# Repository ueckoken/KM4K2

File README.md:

# KagiMod for Koken ver.2 (KM4K2)

KagiMod for Kokenを元にして認証機能を切り離したものです。

RedisにIdmをキャッシュすることによって高速な認証を実現しています。

### Launch

KM4K.serviceはsystemdに登録されています。

```
systemctl status KM4K2
```

で確認

### 環境変数

- `CARD_MANAGER_BASE_URL` : CardManagerのAPIベースURL
- `API_KEY` : CardManagerのAPI-Key
- `REDIS_HOST` : Redisサーバーのホスト名
- `REDIS_PORT` : Redisサーバーのポート番号
- `REDIS_DB` : RedisサーバーのDB番号

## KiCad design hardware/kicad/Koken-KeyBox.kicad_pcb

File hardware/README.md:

# ハードウェア情報
## ピン
- サーボ信号 GPIO12
- LED 成功 GPIO19
- LED 失敗 GPIO26

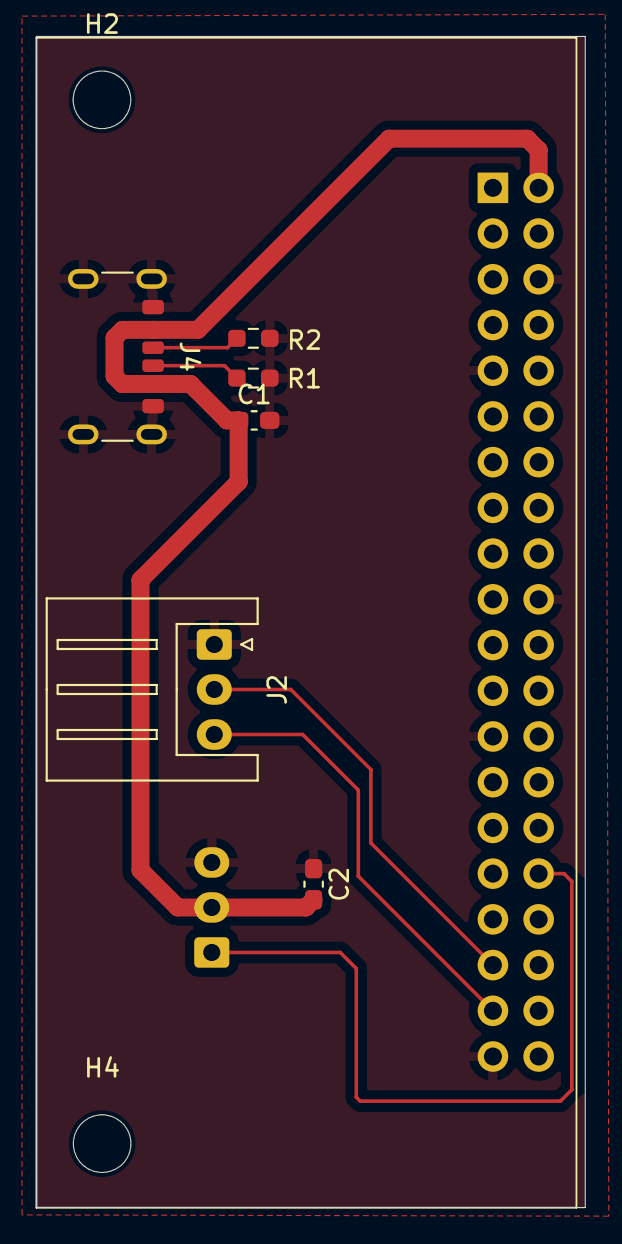
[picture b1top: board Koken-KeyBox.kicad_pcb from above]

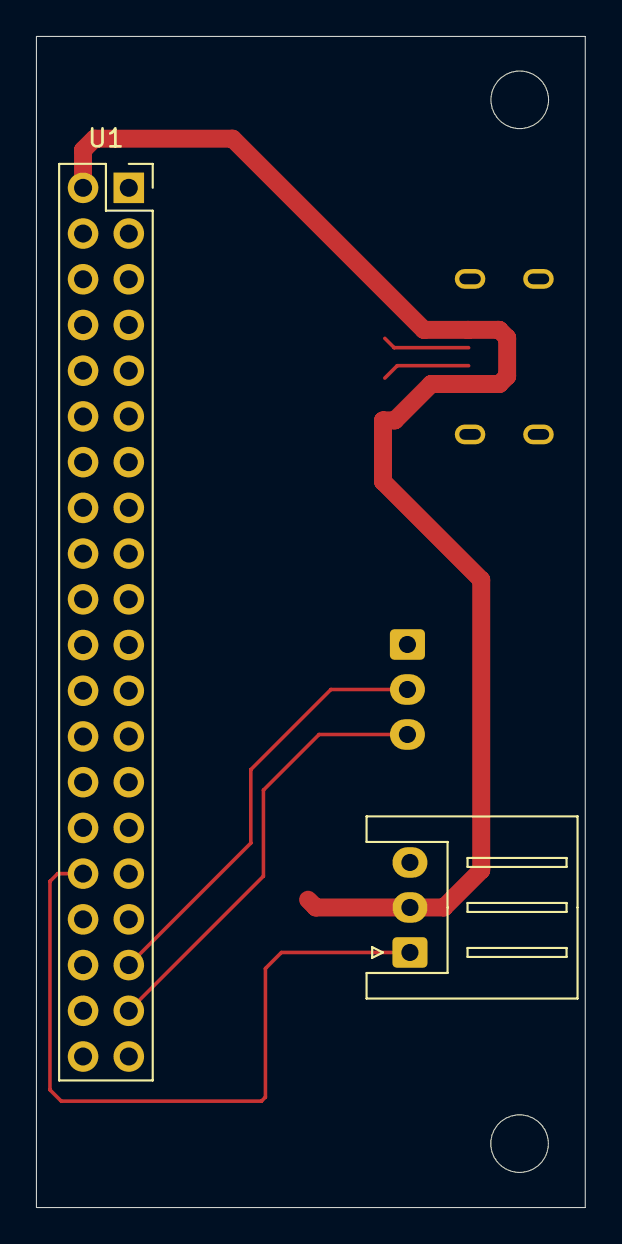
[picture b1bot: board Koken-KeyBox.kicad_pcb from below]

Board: 2 copper layers, 30.5 x 65.1 mm, 10 parts (2 on the bottom side), 7 nets.

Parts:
C1, C2: 2.2u; C_0603_1608Metric_Pad1.08x0.95mm_HandSolder
H2, H4: MountingHole; MountingHole_3.2mm_M3
J2: LED; JST_XH_S3B-XH-A_1x03_P2.50mm_Horizontal
J3: Servo; JST_XH_S3B-XH-A_1x03_P2.50mm_Horizontal
J4: USB_C_Receptacle_PowerOnly_6P; USB_C_Receptacle_GCT_USB4125-xx-x_6P_TopMnt_Horizontal
R1, R2: 5.1k; R_0603_1608Metric_Pad0.98x0.95mm_HandSolder
U1: PinSocket_2x20_P2.54mm_Vertical

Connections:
+5V: C1.1, C2.2, J3.2, J4.A9 (VBUS), J4.B9 (VBUS), U1.2 (5V)
GND: C1.2, C2.1, J2.1, J3.3, J4.A12 (GND), J4.B12 (GND), J4.S1 (SHIELD), R1.2, R2.2, U1.6 (GND), U1.9 (GND), U1.20 (GND), U1.25 (GND), U1.39 (GND)
LED_Failure: J2.3, U1.37 (GPIO26)
LED_Success: J2.2, U1.35 (GPIO19)
unnamed: J4.A5 (CC1), R2.1
unnamed: J4.B5 (CC2), R1.1
Servo_sig: J3.1, U1.32 (GPIO12)

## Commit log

2022-04-28 init
2022-07-31 Delete KM4KwithServer.py
    Deleted obsolete code.
2022-08-04 format
2022-09-10 add test
2022-09-10 run tests on GitHub Actions
2022-09-10 fix python version
2022-09-10 run tests on any pull request
2022-09-10 well testable main
2022-09-30 development container
2022-10-01 remove global mode
2022-10-06 add comments
2022-10-06 refer requirements.txt in requirements-dev.txt
2022-10-06 refer requirements-dev.txt in development container
2023-02-08 package guard
2023-02-08 bump setup-python version
2023-02-08 github actionsのマシンにはpython3.7.15までしか入っていない
2023-02-09 fix version
2023-02-09 fix arm version
2023-02-09 fix ci machine
2023-02-09 add koken sso verify
2023-02-09 update requirements
2023-02-09 fixed requirements
2023-02-09 remove unused ()
2023-02-09 fixed
2023-02-09 add doc about env
2023-02-09 fix merge
2023-02-09 fix test
2023-02-09 fixed typo
2023-02-09 add decode
2023-04-09 update script
2023-04-26 add redis
2023-04-28 install redis-py
2023-04-28 use debian buster as base image
2023-04-28 add redis server to dev containers
2023-04-29 fix tests
2023-04-29 format by black
2023-04-29 softcode Redis connection
2023-04-29 softcode Redis connection in tests
2023-04-29 fix redis service container port binding
2023-04-29 remove unused lines
2023-08-15 lint by ruff
2023-08-15 install ruff as a dev dependency
2023-08-15 fix keyword arguments
2023-08-15 fix typo
2023-08-15 add tests for cache expiration
2023-08-15 fix cache expiration
2023-08-15 single-responsibility class for card manager and dependency injection through arguments
2023-08-15 dependency injection for Redis
2023-08-16 lint, format, and fix wrong conflict resolution
2023-08-17 use timedelta instead of primitive int
2023-08-18 externalize authentication logic and add interface to verify
2023-08-19 pin pip to the current latest version
    ruff requires newer pip
2023-08-19 install git in Dev Container
2023-08-19 flat layout
2023-08-19 lint
2023-08-20 fix patch
2023-08-22 do not hard-code API base URL
2023-08-25 notify errors during verification
2023-09-01 use logging instead of naive print
2023-09-01 fix lint error
2024-04-12 add kicad data
2024-04-12 ピン情報を追加
2024-04-16 コネクタをXHに、電源用コネクタをType-Cに変更
2024-04-19 配線の太さを変更
2024-12-20 requirements-pi2.txtを追加し、必要なライブラリを定義
2024-12-20 requirements-pi2.txtのwiringpiのプラットフォーム条件を修正
2024-12-20 add systemd
